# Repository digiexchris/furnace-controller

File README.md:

# furnace-controller
Simple 5 wire furnace controller using the Lotlin S2 Mini. Intended for ESPHome and Home Assistant or other automation uses.

# Why this exists
It's difficult to find a power supply to run an esp32 or esp8266 (or any 5vdc device for that matter) off of the 24vac transformer typically used in a furnace. This is intended to provide power and 3 relays connected to an esp8266 so that it can run anywhere that the thermostat wires are run in your house (or, as in my case, mounted directly to the furnace cabinet).

# Deets
- Accepts AC or DC input power, up to about 30V maximum. It's possible that it will accept up to 42v, but I have not tested it at that level, and you very likely will let the smoke out. Check the specs on the DC-DC IC for more info.
- 5A Relays, up to 30VDC or 250VAC contacts. 
- Avoids most of the multipurpose pins on the lotlin S2 mini, so you can use them for something else.
- Provides das blinken lighten for telling you if the furnace should be on

# Pinout

| Function | Esp32-S2 Pin |
|----------|--------------|
| Heat     |      IO35    |
| Cool     |      IO18    |
| Fan      |      IO33    |
| WIFI Led |      IO09    |
| Status LED |    IO05    |

# I WANT ONE!

You have a few options:
- whack together one using whatever you have on hand using the schematic (see the kicad project, Kicad 8.0 btw.)
- Shoot me an email at chris@voiditswarranty.com, or see VoidItsWarranty.com, and ask me to make one for you
- Have a board house like jlcpcb make you one. The kicad folder contains the production files used for my first few.

# Example ESPHome config

See furnace-controller.yaml in the root of this project for an example ESPHome config. Once it's up and running in ESPHome, you can use it as a normal set of switches for your thermostat, or any other automation that the relays can support.

# FAQ
- Q: The LEDs are too bright! A: yup, sorry about that
- Q: Will it work on my furnace? A: no idea. Probably, if it's a standard 3-5 wire thermostat and the control circuitry is 24VAC.
- Q: I don't like it. A: Neither does my carpal tunnel.

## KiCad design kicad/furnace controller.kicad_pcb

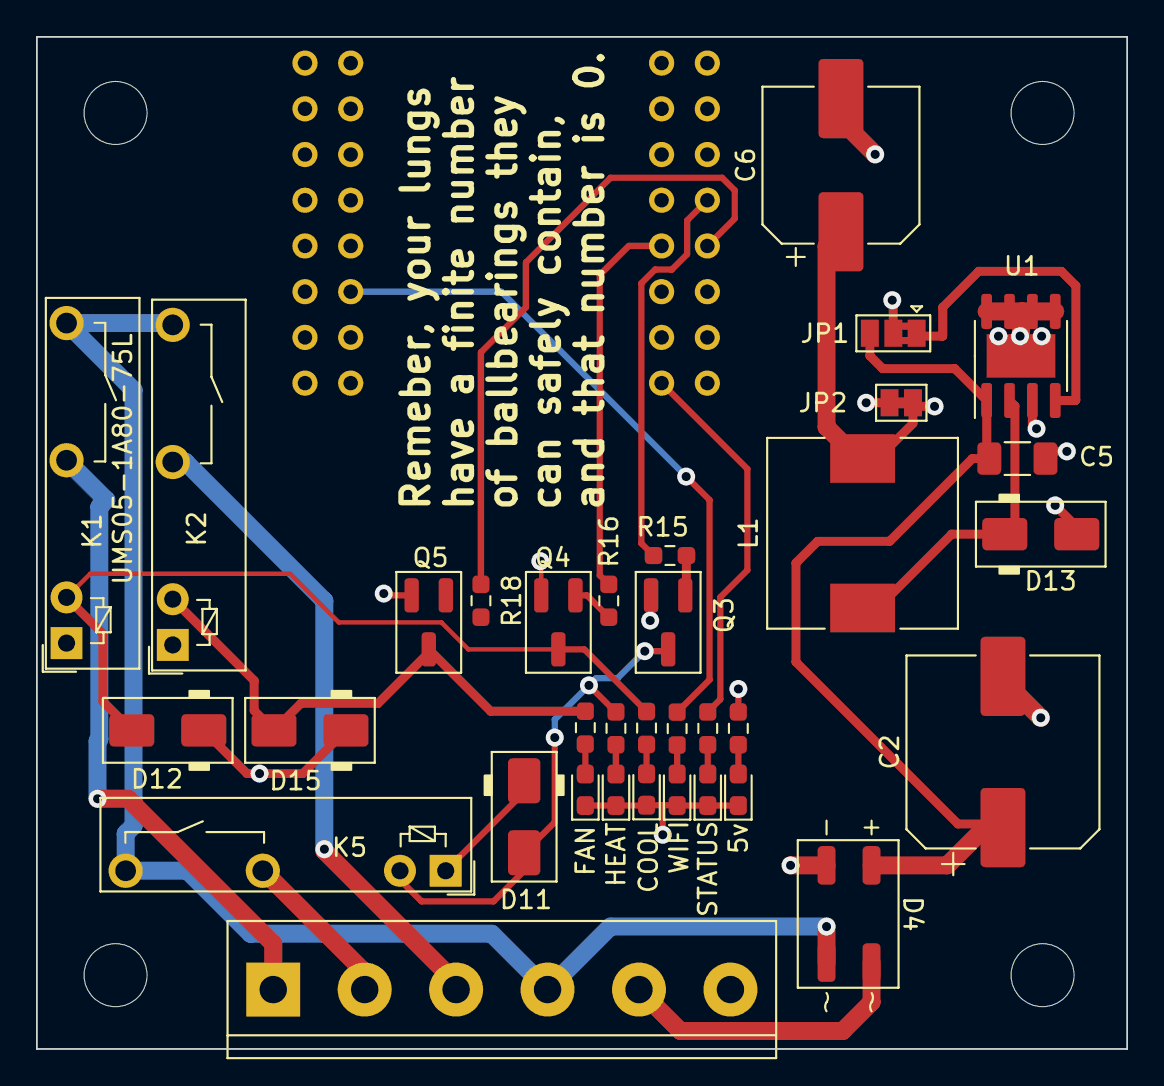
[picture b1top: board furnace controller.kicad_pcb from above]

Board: 4 copper layers, 60.6 x 56.2 mm, 39 parts (1 on the bottom side), 28 nets.

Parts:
C2: 470uf 35v; CP_Elec_10x10.5
C5: 1uf 50v; C_1206_3216Metric_Pad1.33x1.80mm_HandSolder
C6: 180uf 20v; CP_Elec_8x10.5
D1: 5v; LED_0603_1608Metric_Pad1.05x0.95mm_HandSolder
D2: FAN; LED_0603_1608Metric_Pad1.05x0.95mm_HandSolder
D3: HEAT; LED_0603_1608Metric_Pad1.05x0.95mm_HandSolder
D4: MB10S; Diode_Bridge_MBS
D5: STATUS; LED_0603_1608Metric_Pad1.05x0.95mm_HandSolder
D10: COOL; LED_0603_1608Metric_Pad1.05x0.95mm_HandSolder
D11, D12, D13, D15: SS14; D_SMA
D14: WIFI; LED_0603_1608Metric_Pad1.05x0.95mm_HandSolder
H1, H2, H3, H4: MountingHole; MountingHole_3.5mm
J1: Screw_Terminal_01x06; TerminalBlock_bornier-6_P5.08mm
JP1: Jumper_2_Bridged; SolderJumper-3_P1.3mm_Bridged2Bar12_Pad1.0x1.5mm
JP2: Jumper_2_Bridged; SolderJumper-2_P1.3mm_Bridged_Pad1.0x1.5mm
K1, K2, K5: UMS05-1A80-75L; Relay_SPST_TE_PCN-1xxD3MHZ
L1: 68uh 2a; L_10.4x10.4_H4.8
Q3, Q4, Q5: MMBT3904; SOT-23_BigPads
R2k1, R19, R21: 1k; R_0603_1608Metric_Pad0.98x0.95mm_HandSolder
R13, R14, R17: 2k; R_0603_1608Metric_Pad0.98x0.95mm_HandSolder
R15, R16, R18: 470; R_0603_1608Metric_Pad0.98x0.95mm_HandSolder
U1: XL1509-5.0; SOIC-8-1EP_3.9x4.9mm_P1.27mm_EP2.41x3.81mm
U2: mini_esp32; ESP32_lotlin_mini

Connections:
+5V: D11.1 (K), D12.1 (K), D15.1 (K), JP2.2 (B), K1.1, K2.1, K5.1, R19.2, U2.35 (VCC_(USB)), U2.VBUS
/MCU/COOL: R16.1, U2.8 (IO_18/D5)
/MCU/FAN: R18.1, U2.9 (IO_33)
/MCU/HEAT: R15.1, U2.7 (IO_35)
/Power Supply/C: D4.4 (2), J1.5 (C)
/Relays/COOLLED: D12.2 (A), K1.2, Q4.3 (C), R14.2
/Relays/FANLED: D15.2 (A), K2.2, Q5.3 (C), R13.2
/Relays/G: J1.3 (G), K2.3
/Relays/HEATLED: D11.2 (A), K5.2, Q3.3 (C), R17.2
/Relays/W: J1.2 (W), K5.3
/Relays/Y: J1.1 (Y), K1.3
GND: C2.2, C5.2, C6.2, D1.1 (K), D2.1 (K), D3.1 (K), D4.2 (-), D5.1 (K), D10.1 (K), D13.2 (A), D14.1 (K), JP1.2 (C), Q3.2 (E), Q4.2 (E), Q5.2 (E), U1.5 (GND), U1.6 (GND), U1.7 (GND), U1.8 (GND), U1.9 (GND), U2.33 (GND), U2.GND
LINE: D4.3 (1), J1.4 (R), K1.4, K2.4, K5.4
unnamed: D1.2 (A), R19.1
unnamed: D2.2 (A), R13.1
unnamed: D3.2 (A), R17.1
unnamed: C2.1, C5.1, D4.1 (+), JP1.3 (B), U1.1 (VIN)
unnamed: D5.2 (A), R21.1
unnamed: D10.2 (A), R14.1
unnamed: D13.1 (K), L1.1, U1.2 (OUT)
unnamed: D14.2 (A), R2k1.1
unnamed: JP1.1 (A), U1.4 (~EN)
unnamed: C6.1, JP2.1 (A), L1.2, U1.3 (FB)
unnamed: Q3.1 (B), R15.2
unnamed: Q4.1 (B), R16.2
unnamed: Q5.1 (B), R18.2
unnamed: R21.2, U2.14 (IO_05/D8)
unnamed: R2k1.2, U2.17 (IO_09/SD2)

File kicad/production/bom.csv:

Designator,Footprint,Quantity,Value,LCSC Part #
C2,CP_Elec_10x10.5,1,470uf 35v,
C5,1206,1,1uf 50v,
C6,CP_Elec_8x10.5,1,180uf 20v,
D1,0603,1,5v,C2286
D10,0603,1,COOL,C72038
"D11, D12, D13, D15",D_SMA,4,SS14,C2480
D14,0603,1,WIFI,C72038
D2,0603,1,FAN,C72038
D3,0603,1,HEAT,C2286
D4,Diode_Bridge_MBS,1,MB10S,C2488
D5,0603,1,STATUS,C72038
"H1, H2, H3, H4",MountingHole_3.5mm,4,MountingHole,
J1,TerminalBlock_bornier-6_P5.08mm,1,Screw_Terminal_01x06,C5188023
JP1,SolderJumper-3_P1.3mm_Bridged2Bar12_Pad1.0x1.5mm,1,Jumper_2_Bridged,
JP2,SolderJumper-2_P1.3mm_Bridged_Pad1.0x1.5mm,1,Jumper_2_Bridged,
"K1, K2, K5",Relay_SPST_TE_PCN-1xxD3MHZ,3,UMS05-1A80-75L,C28975
L1,L_10.4x10.4_H4.8,1,68uh 2a,
"Q3, Q4, Q5",SOT-23_BigPads,3,MMBT3904,C20526
R13,0603,1,2k,C17437
R14,0603,1,2k,C17408
"R15, R16, R18",0603,3,470,C17710
R17,0603,1,2k,C17471
"R19, R21",0603,2,1k,C17720
R2k1,0603,1,1k,C17415
U1,SOIC-8-1EP_3.9x4.9mm_P1.27mm_EP2.41x3.81mm,1,XL1509-5.0,
U2,ESP32_lotlin_mini,1,mini_esp32,

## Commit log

2024-03-02 Initial configuration
